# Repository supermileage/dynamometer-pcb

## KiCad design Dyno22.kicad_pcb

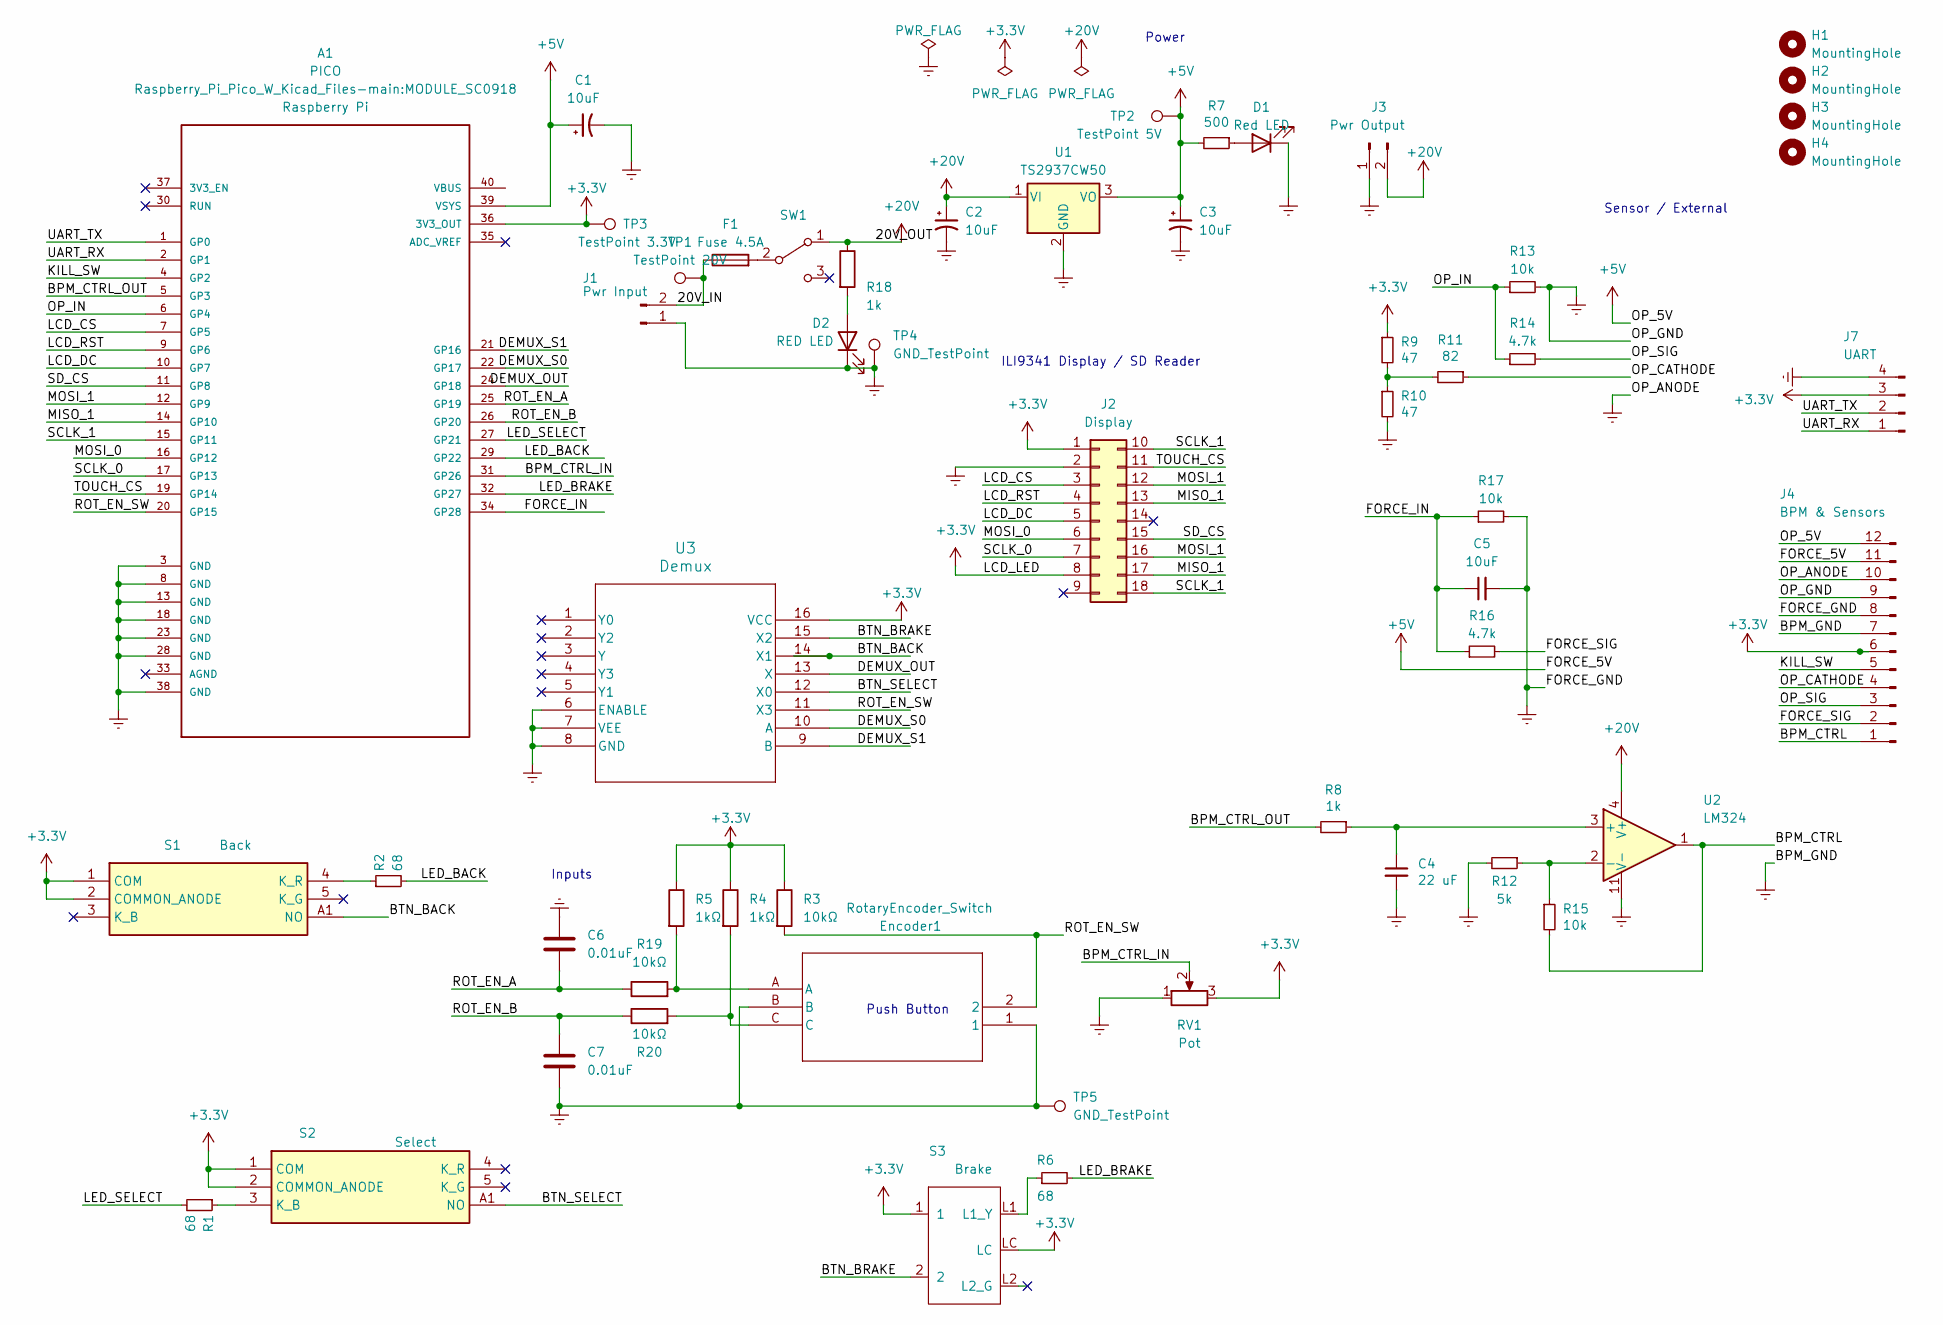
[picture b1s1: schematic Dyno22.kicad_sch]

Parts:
A1: PICO; MODULE_SC0918; PARTREV 1.6
C1, C3: 10uF; C_1206_3216Metric
C2: 10uF; CAP_293D-C_VSS
C4: 22 uF; C_0805_2012Metric
C5: 10uF; C_0805_2012Metric
C6, C7: 0.01uF; C_0603_1608Metric
D1: Red LED; LED_0805_2012Metric
D2: RED LED; LED_0805_2012Metric
Encoder1: RotaryEncoder_Switch; TO_215F-S0024
F1: Fuse 4.5A; Fuse_1206_3216Metric
H1, H2, H3, H4: MountingHole; MountingHole_3.2mm_M3
J1: Pwr Input; Molex_Nano-Fit_105313-xx02_1x02_P2.50mm_Horizontal
J2: Display; ILI9351_Large_Display
J3: Pwr Output; Molex_Nano-Fit_105313-xx02_1x02_P2.50mm_Horizontal
J4: BPM & Sensors; Molex_Nano-Fit_105314-xx12_2x06_P2.50mm_Horizontal
J7: UART; Molex_Nano-Fit_105314-xx04_2x02_P2.50mm_Horizontal
R1, R2, R6: 68; R_0805_2012Metric
R3, R19, R20: 10kΩ; R_0805_2012Metric
R4, R5: 1kΩ; R_0805_2012Metric
R7: 500; R_0805_2012Metric
R8, R18: 1k; R_0805_2012Metric
R9, R10: 47; R_0805_2012Metric
R11: 82; R_0805_2012Metric
R12: 5k; R_0805_2012Metric
R13, R15, R17: 10k; R_0805_2012Metric
R14, R16: 4.7k; R_0805_2012Metric
RV1: Pot; Potentiometer_Vishay_148-149_Single_Vertical
S1: Back; KP0115ANBKG03RGBP3SJB; Mouser Part Number 633-5ANBKG03RGBP3SJB
S2: Select; KP0115ANBKG03RGBP3SJB; Mouser Part Number 633-5ANBKG03RGBP3SJB
S3: Brake; LP11EE1NCSYG
SW1: SW_DPST_x2; SW_300SP1J1BLKM2QE
TP1: TestPoint 20V; TestPoint_Plated_Hole_D2.0mm
TP2: TestPoint 5V; TestPoint_Plated_Hole_D2.0mm
TP3: TestPoint 3.3V; TestPoint_Plated_Hole_D2.0mm
TP4, TP5: GND_TestPoint; TestPoint_Plated_Hole_D2.0mm
U1: TS2937CW50; SOT-223-3_TabPin2
U2: LM324; DIP-14_W7.62mm
U3: Demux; SOIC-16WB_ONS

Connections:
+3.3V: A1.36 (3V3_OUT), J2.1, J2.8, J4.6, J7.3, R3.1, R4.1, R5.1, R9.1, RV1.3, S1.1 (COM), S1.2 (COMMON_ANODE), S2.1 (COM), S2.2 (COMMON_ANODE), S3.1, S3.LC, TP3.1, U3.16 (VCC); also elsewhere on the board
+5V: A1.39 (VSYS), C1.1, C3.1, J4.11, J4.12, R7.2, TP2.1, U1.3 (VO)
+24V: C2.1, J3.2, R18.1, SW1.1 (A), U1.1 (VI), U2.4 (V+); also elsewhere on the board
/20V_IN: F1.1, J1.2, TP1.1
/BPM_CTRL: J4.1, R15.2, U2.1
/BPM_CTRL_IN: A1.31 (GP26), RV1.2
/BPM_CTRL_OUT: A1.5 (GP3), R8.2
/BTN_BACK: S1.A1 (NO), U3.14 (X1); also elsewhere on the board
/BTN_BRAKE: S3.2, U3.15 (X2)
/BTN_SELECT: S2.A1 (NO), U3.12 (X0); also elsewhere on the board
/DEMUX_OUT: A1.24 (GP18), U3.13 (X)
/DEMUX_S0: A1.22 (GP17), U3.10 (A)
/DEMUX_S1: A1.21 (GP16), U3.9 (B)
/FORCE_IN: A1.34 (GP28), C5.1, R16.1, R17.1
/FORCE_SIG: J4.2, R16.2
/KILL_SW: A1.4 (GP2), J4.5
/LCD_CS: A1.7 (GP5), J2.3
/LCD_DC: A1.10 (GP7), J2.5
/LCD_RST: A1.9 (GP6), J2.4
/LED_BACK: A1.29 (GP22), R2.2
/LED_BRAKE: A1.32 (GP27), R6.2
/LED_SELECT: A1.27 (GP21), R1.2
/MISO_1: A1.14 (GP10), J2.13, J2.17
/MOSI_0: A1.16 (GP12), J2.6
/MOSI_1: A1.12 (GP9), J2.12, J2.16
/OP_CATHODE: J4.4, R11.1
/OP_IN: A1.6 (GP4), R13.1, R14.1
/OP_SIG: J4.3, R14.2
/ROT_EN_A: A1.25 (GP19), C6.2, R19.1
/ROT_EN_B: A1.26 (GP20), C7.1, R20.1
/ROT_EN_SW: A1.20 (GP15), Encoder1.2, R3.2, U3.11 (X3); also elsewhere on the board
/SCLK_0: A1.17 (GP13), J2.7
/SCLK_1: A1.15 (GP11), J2.10, J2.18
/SD_CS: A1.11 (GP8), J2.15
/TOUCH_CS: A1.19 (GP14), J2.11
/UART_RX: A1.2 (GP1), J7.1
/UART_TX: A1.1 (GP0), J7.2
Earth: A1.3 (GND), A1.8 (GND), A1.13 (GND), A1.18 (GND), A1.23 (GND), A1.28 (GND), A1.38 (GND), C1.2, C2.2, C3.2, C4.2, C5.2, C6.1, C7.2, D1.1 (K), D2.1 (K), Encoder1.1, Encoder1.B, J1.1, J2.2, J3.1, J4.7, J4.8, J4.9, J4.10, J7.4, R10.2, R12.2, R13.2, R17.2, RV1.1, TP4.1, TP5.1, U1.2 (GND), U2.11 (V-), U3.6 (ENABLE), U3.7 (VEE), U3.8 (GND); also elsewhere on the board
unnamed: D1.2 (A), R7.1
unnamed: D2.2 (A), R18.2
unnamed 40: Encoder1.A, R5.2, R19.2; also elsewhere on the board
unnamed 41: Encoder1.C, R4.2, R20.2; also elsewhere on the board
unnamed: R9.2, R10.1, R11.2
unnamed 43: R2.1, S1.4 (K_R); also elsewhere on the board
unnamed 44: R1.1, S2.3 (K_B); also elsewhere on the board
unnamed: R6.1, S3.L1 (L1_Y)
unnamed 46: F1.2, SW1.2 (B); also elsewhere on the board
unnamed: C4.1, R8.1, U2.3 (+)
unnamed: R12.1, R15.1, U2.2 (-)

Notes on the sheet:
Power
Push Button
Sensor / External
ILI9341 Display / SD Reader
Inputs

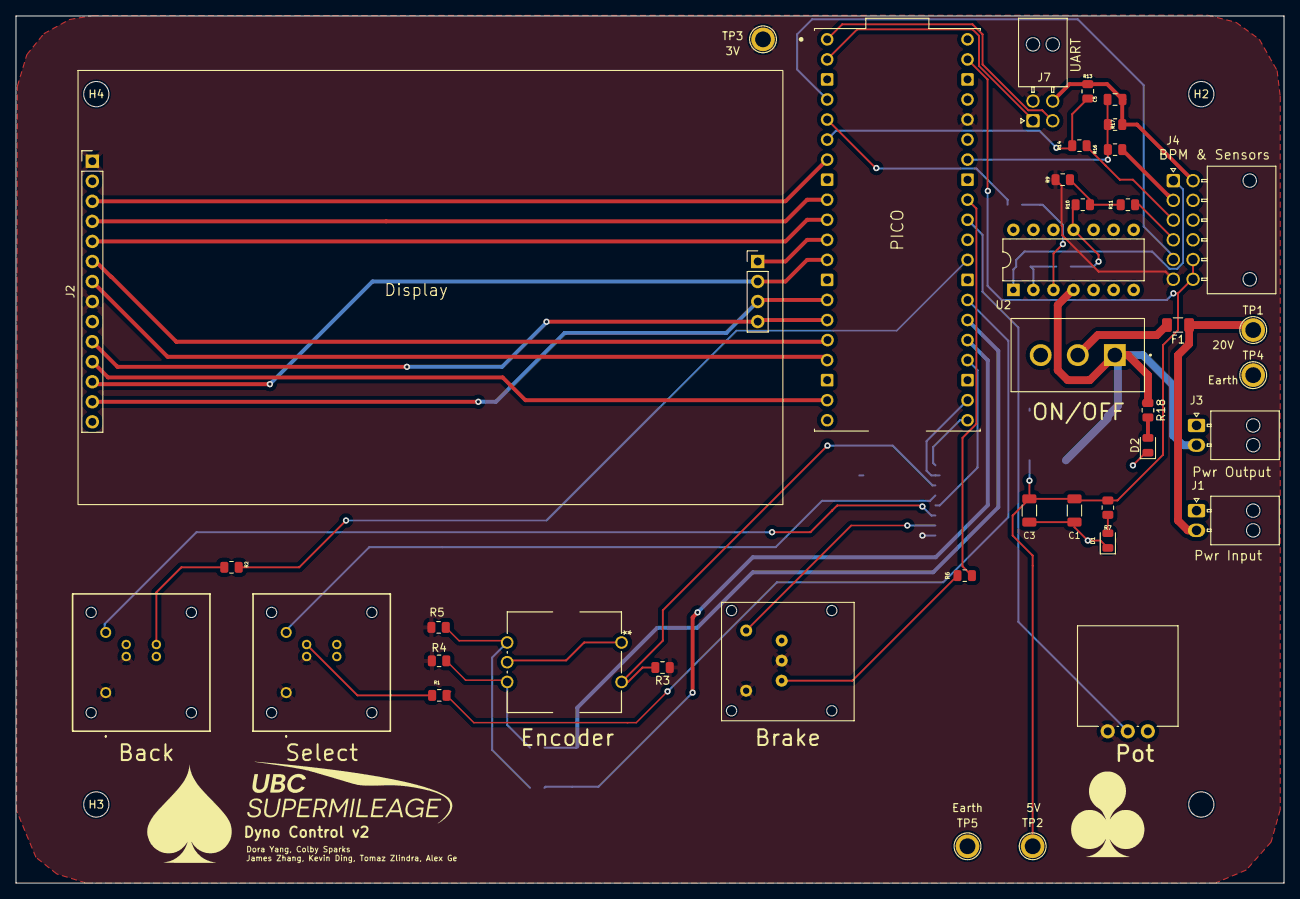
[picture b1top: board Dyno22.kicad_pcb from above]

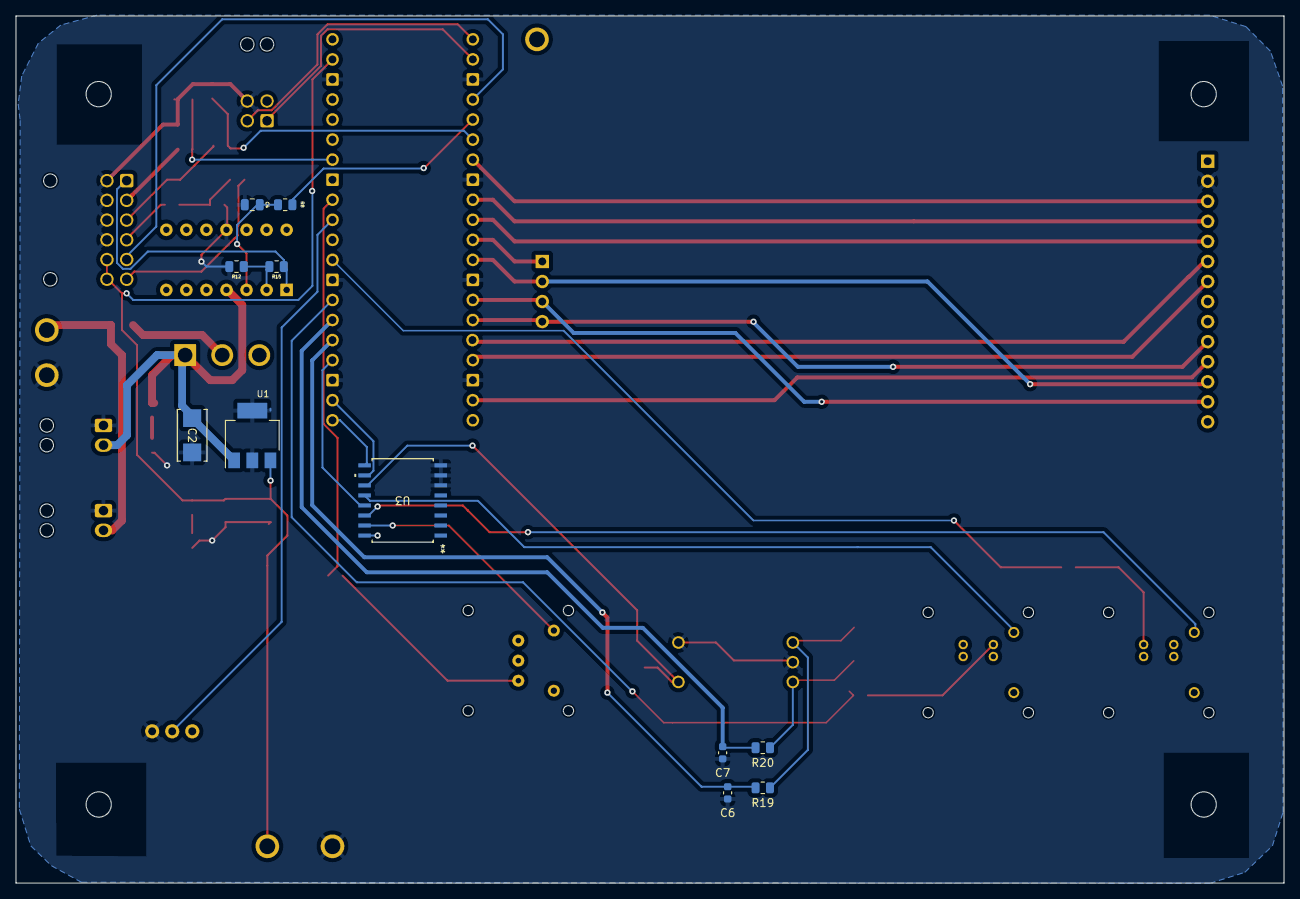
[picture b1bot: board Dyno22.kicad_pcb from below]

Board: 2 copper layers, 160.7 x 109.9 mm, 55 parts (11 on the bottom side), 49 nets.

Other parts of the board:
Back: Back; KP0115ANBKG03RGBP3SJB
Encoder: RotaryEncoder_Switch; TO_215F-S0024
GW: LOGO
ON/OFF: SW_DPST_x2; SW_300SP1J1BLKM2QE
Select: Select; KP0115ANBKG03RGBP3SJB

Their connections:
+3.3V: Back.1 (COM), Back.2 (COMMON_ANODE), Select.1 (COM), Select.2 (COMMON_ANODE); also elsewhere on the board
+24V: ON/OFF.1 (A); also elsewhere on the board
/BTN_BACK: Back.A1 (NO); also elsewhere on the board
/BTN_SELECT: Select.A1 (NO); also elsewhere on the board
/ROT_EN_SW: Encoder.2; also elsewhere on the board
Earth: Encoder.1, Encoder.B; also elsewhere on the board
unnamed 40: Encoder.A; also elsewhere on the board
unnamed 41: Encoder.C; also elsewhere on the board
unnamed 43: Back.4 (K_R); also elsewhere on the board
unnamed 44: Select.3 (K_B); also elsewhere on the board
unnamed 46: ON/OFF.2 (B); also elsewhere on the board

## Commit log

2023-02-12 Adding Dyno KiCad Project Files
2023-02-21 Updates schematic to include pico w, lcd display and ui inputs
2023-02-21 Fixes some labels--adds new label for 20V input
2023-02-21 Adds 5 -> 3.3V conversion for force and optical sensors
2023-02-21 Adds voltage regulator to power input
2023-02-21 Adds connections for all button pins
2023-02-21 Small change
2023-02-21 Fixes pin headers for lcd display
2023-02-22 Modifies op amp circuit -- 3.3V -> 10V pwm
2023-02-22 uart labels assigned to wrong pins
2023-02-23 Adds graphics to pcb
2023-02-23 Adds wider traces and high-voltage capacitor to pwr circuit
2023-02-23 Rearranges components on pcb - final arrangement
2023-03-11 Uploading changes to PCB and Schematic
    * Removed button pull down resistors
    * Updated rotary encoder and potentiometer footprints
    * Moved display (and minor layout changes of other components)
    * Added mounting holes to support rotary encoder
2023-03-18 PCB Layout Done
2023-04-08 PCB Update: new connectors, UART, e-stop, buttons moved
2023-04-08 Eliminated PCB design rule check errors
2023-05-04 adjusts positioning of buttons and screen -- adds names to silkscreen layer
2023-05-04 Adds project-local copies of newly added symbols and footprints
2023-05-04 Adds proper footprint for LM324
2023-10-28 Fix potentiometer footprint#17
2023-11-04 Fix Rotary Encoder Footprint #14
2023-11-11 Rerouted some traces for DRC and made ROT pins consecutive
2023-11-19 Changes the rotary encoder input pins, spacing adjustments to encoder and potentiometer, increase in silkscreen text size.
2023-11-25 Fixed traces DRC
2023-12-02 moving traces for the pot
2024-01-15 Schematic modifications, including additional switch, fuse and LED
2024-01-16 schematic changes v2
2024-01-18 moved LCD PICO, updated traces for buttons encoder pot
2024-01-19 moved components and fixed connections to accomodate for new pico location and power components
2024-01-20 made some passive components 0805 and changed some routing
2024-01-21 Added demux changed LED location changed some Rs
2024-01-25 Amplifier footprint changes
2024-01-27 Changed routing and component placement AGAIN
2024-01-27 Forgot to save schematic changes
2024-01-27 Fix the earth, the earth is our home
2024-01-27 PCB trace routing changes
2024-01-27 Trace changes
2024-01-29 Through hole adjustments and some routing changes
2024-01-31 move around the rot encoder
2024-02-03 updated encoder
2024-02-03 added encoder filter circuit
2024-02-04 eliminated demux dead zone
2024-02-04 gerber output
